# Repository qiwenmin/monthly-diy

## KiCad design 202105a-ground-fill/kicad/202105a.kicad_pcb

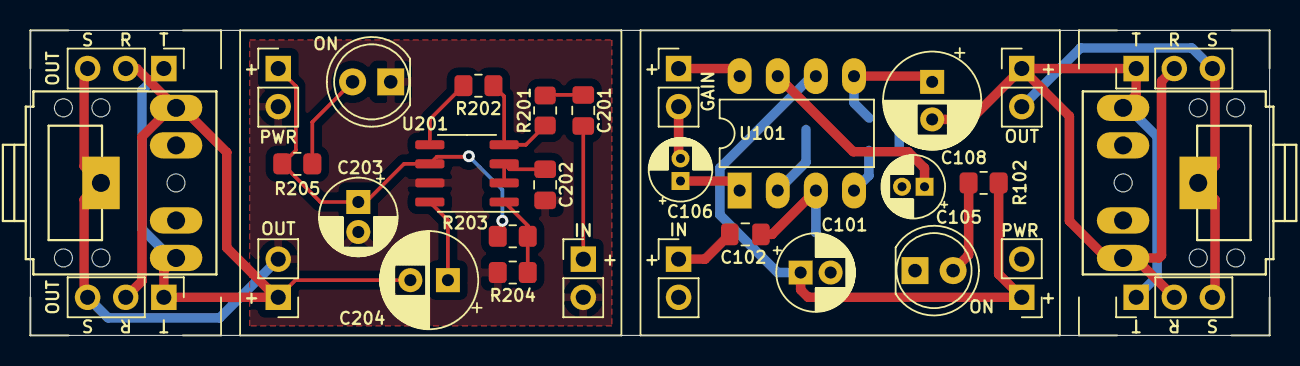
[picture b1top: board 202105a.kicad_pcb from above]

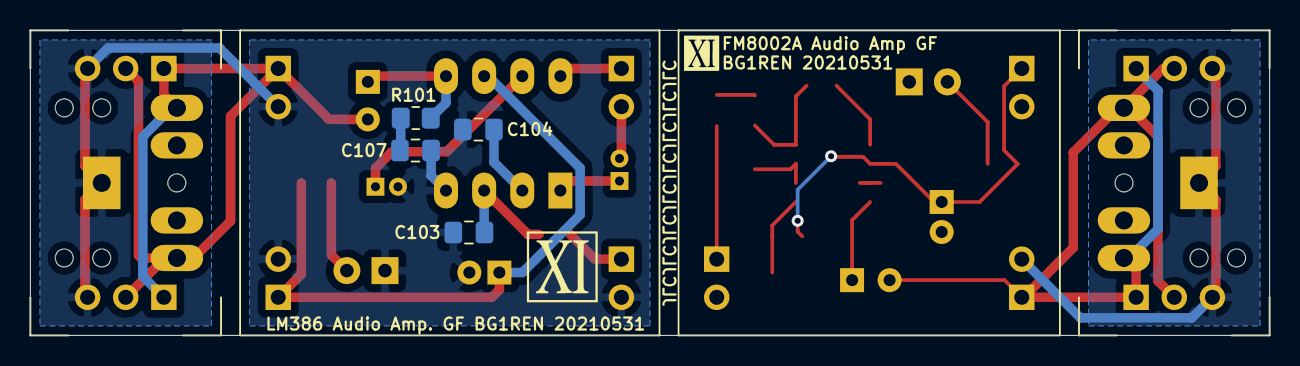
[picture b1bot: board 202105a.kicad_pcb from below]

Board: 2 copper layers, 82.5 x 20.3 mm, 36 parts (4 on the bottom side), 24 nets.

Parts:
C101, C203: 100u; CP_Radial_D5.0mm_P2.00mm
C102, C104: 0.27u; C_0805_2012Metric_Pad1.18x1.45mm_HandSolder
C103: 47p; C_0805_2012Metric_Pad1.18x1.45mm_HandSolder
C105, C106: 10u; CP_Radial_D4.0mm_P1.50mm
C107: 0.1u; C_0805_2012Metric_Pad1.18x1.45mm_HandSolder
C108, C204: 470u; CP_Radial_D6.3mm_P2.50mm
C201: 0.39u; C_0805_2012Metric_Pad1.18x1.45mm_HandSolder
C202: 1u; C_0805_2012Metric_Pad1.18x1.45mm_HandSolder
D101, D201: ON; LED_D5.0mm
J101, J201: PWR; PinHeader_1x02_P2.54mm_Vertical
J102, J202: IN; PinHeader_1x02_P2.54mm_Vertical
J103, J203: OUT; PinHeader_1x02_P2.54mm_Vertical
J104: GAIN; PinHeader_1x02_P2.54mm_Vertical
J105, J204: OUT; Tayda_3.5mm_stereo_TRS_jack_A-853
J106, J107, J205, J206: OUT; PinHeader_1x03_P2.54mm_Vertical
R101: 10; R_0805_2012Metric_Pad1.20x1.40mm_HandSolder
R102, R205: 22K; R_0805_2012Metric_Pad1.20x1.40mm_HandSolder
R201: 20K; R_0805_2012Metric_Pad1.20x1.40mm_HandSolder
R202: 470K; R_0805_2012Metric_Pad1.20x1.40mm_HandSolder
R203, R204: 0; R_0805_2012Metric_Pad1.20x1.40mm_HandSolder
U101: LM386; DIP-8_W7.62mm_LongPads
U201: FM8002A; SOIC-8_3.9x4.9mm_P1.27mm

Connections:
/100_+9V: C101.1, J101.1, R102.2, U101.6
/100_AF_IN: C102.2, J102.1
/100_AF_OUT: C108.2, J103.1, J105.R, J105.T, J106.1, J106.2, J107.1, J107.2
/100_GAIN+: C106.1, U101.1
/100_GAIN-: J104.1, U101.8
/100_GND: C101.2, C103.1, C104.2, C105.2, C107.2, D101.1, J101.2, J102.2, J103.2, J105.S, J106.3, J107.3, U101.4
/200_AF_IN: C201.2, J202.1
/200_AF_OUT: C204.2, J203.1, J204.R, J204.T, J205.1, J205.2, J206.1, J206.2
/200_GND: C202.2, C203.2, D201.1, J201.2, J202.2, J203.2, J204.S, J205.3, J206.3, R204.1, U201.7
/200_VDD: C203.1, J201.1, R203.2, R205.2, U201.6
unnamed: C102.1, C103.2, U101.3
unnamed: C104.1, U101.2
unnamed: C105.1, U101.7
unnamed: C106.2, J104.2
unnamed: C107.1, R101.2
unnamed: C108.1, R101.1, U101.5
unnamed: C201.1, R201.2
unnamed: C202.1, U201.2, U201.3
unnamed: C204.1, U201.8
unnamed: D101.2, R102.1
unnamed: D201.2, R205.1
unnamed: R201.1, R202.1, U201.4
unnamed: R202.2, U201.5
unnamed: R203.1, R204.2, U201.1
